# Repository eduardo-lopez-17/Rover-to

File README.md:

# Rover-to

## Descripción general

Este repositorio reúne varios proyectos de `PlatformIO` orientados a telecomunicaciones, procesamiento de señal digital (DSP), navegación por visión e integración de sensores con ESP32-S3.

Las carpetas principales son:

- `DSP_Transmisor` - firmware para transmisores y receptores de telemetría / DSP.
- `Rover` - firmware del rover de navegación basado en VIO y ESP-NOW.
- `GPS` - proyecto independiente de GPS.
- `Pantalla` - proyecto independiente de visualización.
- `Receptor` - firmware receptor para la telemetría.

## Estructura del workspace

- `DSP_Transmisor/` contiene varios entornos de compilación para:
  - `dsp_esp32_s3` - simulación DSP de señales IMU en ESP32-S3.
  - `telecom_esp32_s3` - integración de sensores y transmisión de telemetría.
  - `telecom_xiao_s3` - transmisor maestro en Seeed XIAO ESP32-S3.
  - `receiver_xiao_s3` - receptor XIAO ESP32-S3 que recibe datos por ESP-NOW y RFM69.
- `Rover/` contiene el firmware del rover con tareas FreeRTOS, visión por flujo óptico, navegación VIO y transmisión inalámbrica.

## Cómo usar

1. Abre la carpeta raíz en VS Code.
2. Selecciona el proyecto que deseas compilar (`DSP_Transmisor` o `Rover`).
3. Usa `PlatformIO > Build` o la terminal:
   - `platformio run -e dsp_esp32_s3`
   - `platformio run -e telecom_esp32_s3`
   - `platformio run -e telecom_xiao_s3`
   - `platformio run -e receiver_xiao_s3`
   - `platformio run -e seeed_xiao_esp32s3`

## Documentación específica

- `DSP_Transmisor/README.md` - explicación detallada del transmisor, receptor y modos de compilación.
- `Rover/README.md` - explicación de la arquitectura VIO, tareas y comunicaciones del rover.

---

> Nota: `sensor_payload.h` se usa como estructura de datos compartida y debe mantenerse idéntica entre transmisor y receptor para garantizar la interoperabilidad.

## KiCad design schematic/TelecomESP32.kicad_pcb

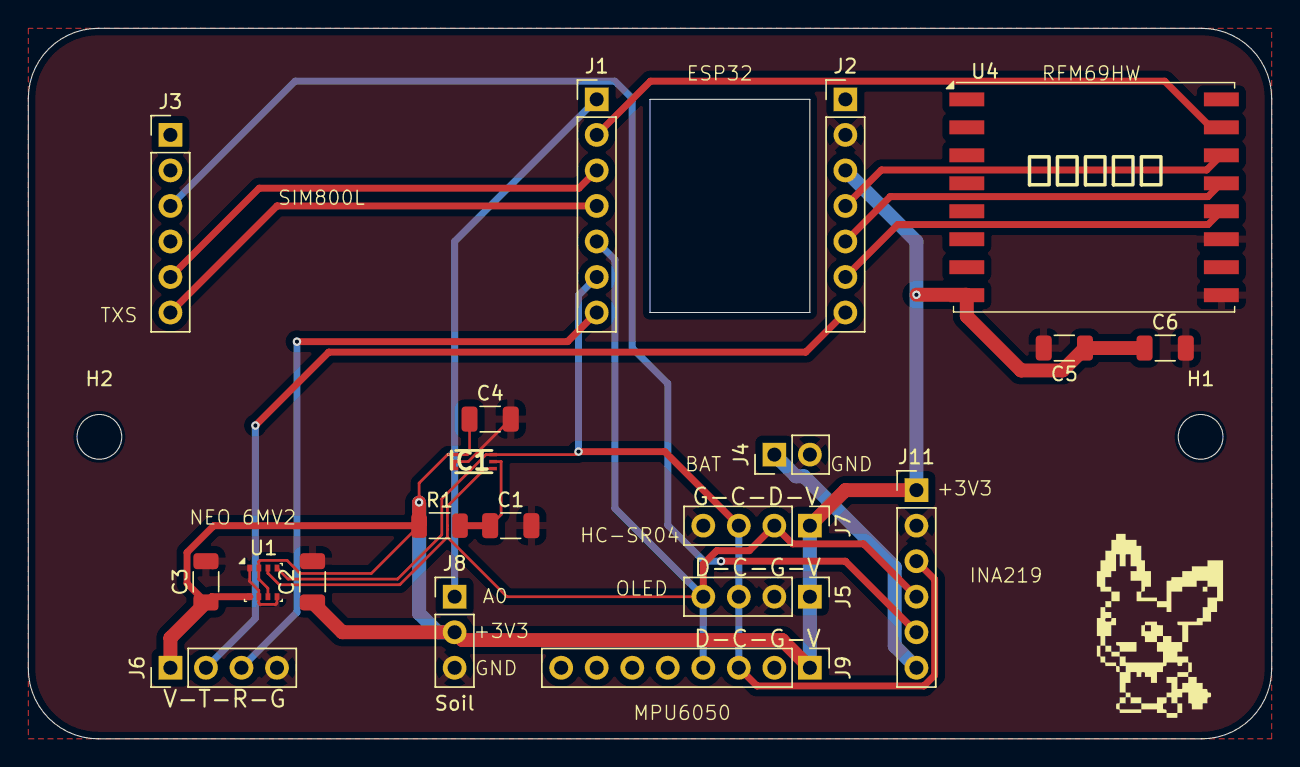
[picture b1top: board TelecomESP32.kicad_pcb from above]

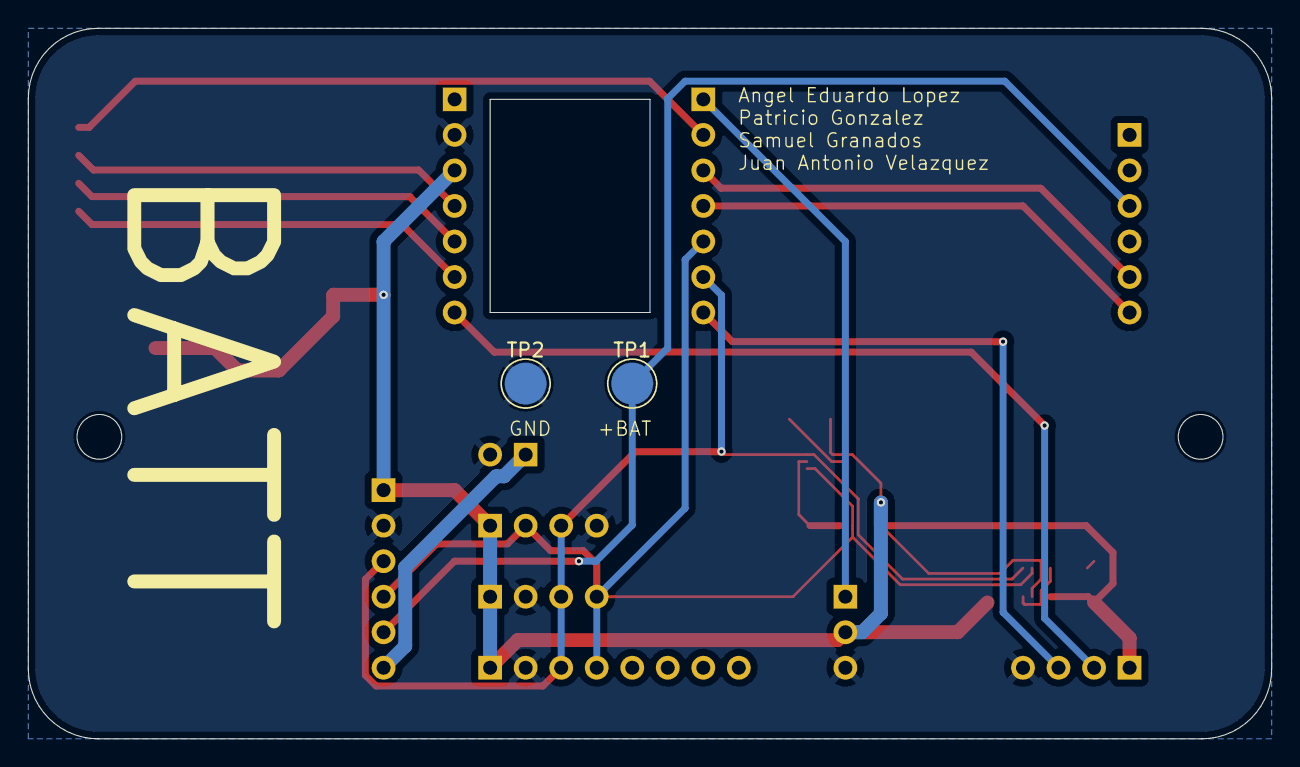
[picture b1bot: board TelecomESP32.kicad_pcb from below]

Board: 2 copper layers, 88.9 x 50.8 mm, 25 parts (2 on the bottom side), 16 nets.

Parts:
C1, C2, C3, C4, C5: 0.1uF; C_1206_3216Metric
C6: 10uF; C_1206_3216Metric
H1, H2, H2#2: MountingHole; MountingHole_3.2mm_M3
IC1: BH1750FVI-TR; WSOF6
J1: ESP32 XIAO LEFT; PinHeader_1x07_P2.54mm_Vertical
J2: ESP32 XIAO RIGHT; PinHeader_1x07_P2.54mm_Vertical
J3: SIM800L; PinHeader_1x06_P2.54mm_Vertical
J4: BAT; PinHeader_1x02_P2.54mm_Vertical
J5: OLED; PinHeader_1x04_P2.54mm_Vertical
J6: NEO6MV2; PinHeader_1x04_P2.54mm_Vertical
J7: HC-SR04P; PinHeader_1x04_P2.54mm_Vertical
J8: Soil; PinHeader_1x03_P2.54mm_Vertical
J9: MPU6050; PinHeader_1x08_P2.54mm_Vertical
J11: INA219; PinHeader_1x06_P2.54mm_Vertical
R1: 1K; R_1206_3216Metric
TP1: +BATT; TestPoint_Pad_D3.0mm
TP2: GND; TestPoint_Pad_D3.0mm
U1: BME280; Bosch_LGA-8_2.5x2.5mm_P0.65mm_ClockwisePinNumbering
U4: RFM69HW; HOPERF_RFM69HW

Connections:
+3V3: C2.1, C3.1, C4.1, C5.1, C6.1, IC1.1 (VCC), J2.3, J5.1, J6.1, J7.1, J8.2, J9.1, J11.1, R1.1, U1.2 (CSB), U1.6 (VDDIO), U1.8 (VDD), U4.8 (3.3V)
+BATT: J3.3, J11.5, TP1.1
/+Vin: J4.1, J11.6
A0: J1.1, J8.1
GND: C1.2, C2.2, C3.2, C4.2, C5.2, C6.2, IC1.2 (ADDR), IC1.3 (GND), J2.2, J4.2, J5.2, J6.4, J7.4, J8.3, J9.2, J11.2, TP2.1, U1.1 (GND), U1.5 (SDO), U1.7 (GND), U4.9 (GND), U4.11 (GND)
MISO: J2.5, U4.13 (MISO)
MOSI: J2.4, U4.14 (MOSI)
NSS: J1.2, U4.15 (NSS)
unnamed: C1.1, IC1.5 (DVI), R1.2
RX: J1.7, J6.3
RXS: J1.3, J3.5
SCK: J2.6, U4.12 (SCK)
SCL: IC1.6 (SCL), J1.6, J5.3, J7.3, J9.3, J11.3, U1.4 (SCK)
SDA: IC1.4 (SDA), J1.5, J5.4, J7.2, J9.4, J11.4, U1.3 (SDI)
TX: J2.7, J6.2
TXS: J1.4, J3.6

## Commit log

2026-05-14 Initial Project
2026-05-14 Added schematic of the project
2026-05-15 Add project description to README
2026-05-15 Receiver and transmitter
    Receiver and transmitter
2026-05-15 AutogeneratedFiles
2026-05-15 BNO-Conection
2026-05-15 Added comment test
    Test test test
2026-05-15 Add GPS test file
    Programacion de modulo NEO-6M-0-001
2026-05-15 Add GPS module code for ESP32
2026-05-15 Codigo GPS funcional
2026-05-20 Added moisture sensor library and functions
2026-05-20 separacion de proyectos
2026-05-20 minor changes
2026-05-20 ultrasonic header file was moved to include dir
2026-05-25 Created the Tasks file and created some tasks
2026-05-26 archivos gps y ultrasonico
2026-05-26 sensor de luz
2026-05-27 Pantalla
2026-05-27 oled receptor
2026-06-01 mas sensores
2026-06-01 receptor
2026-06-01 cambio a ingles
2026-06-01 ingles de telecom
2026-06-02 inclusion de todos los sensores
2026-06-02 quite la pantalla
2026-06-02 debug-primer guardado de fotos en sd
2026-06-02 cambios GPS
2026-06-03 se agrego mac address del xiao
2026-06-03 Created task header file, with config header file
2026-06-03 Added serial initializer and linx kernel coding style
2026-06-03 clang format
2026-06-03 Fix formatting issues
2026-06-03 added imu and camera files, and imu orientation logic
2026-06-03 added pins definitions to camera
2026-06-03 Added camera and flow code
2026-06-03 Added tasks defines
2026-06-03 navigation files added
2026-06-04 formato kernel
2026-06-04 lora medio jalando
2026-06-04 ya jala i2c
2026-06-05 Rover positioning
2026-06-05 Cambios a camara
2026-06-05 Enhanced reliabity
2026-06-05 Increased camera framerate by adding a second buffer
2026-06-05 se implementó red neuronal, se terminaron de poner features
2026-06-07 Calibrated and factor correction
2026-06-08 Added ESP NOW Comm, does not work yet
2026-06-09 mmm jalo casi todo
2026-06-09 Wireless COM FIXED
2026-06-09 ESP NOW implemented
2026-06-09 espnow
2026-06-09 wireless
2026-06-09 payload
2026-06-09 Fixed Transmissor
2026-06-10 Calibrated Factor Correction
